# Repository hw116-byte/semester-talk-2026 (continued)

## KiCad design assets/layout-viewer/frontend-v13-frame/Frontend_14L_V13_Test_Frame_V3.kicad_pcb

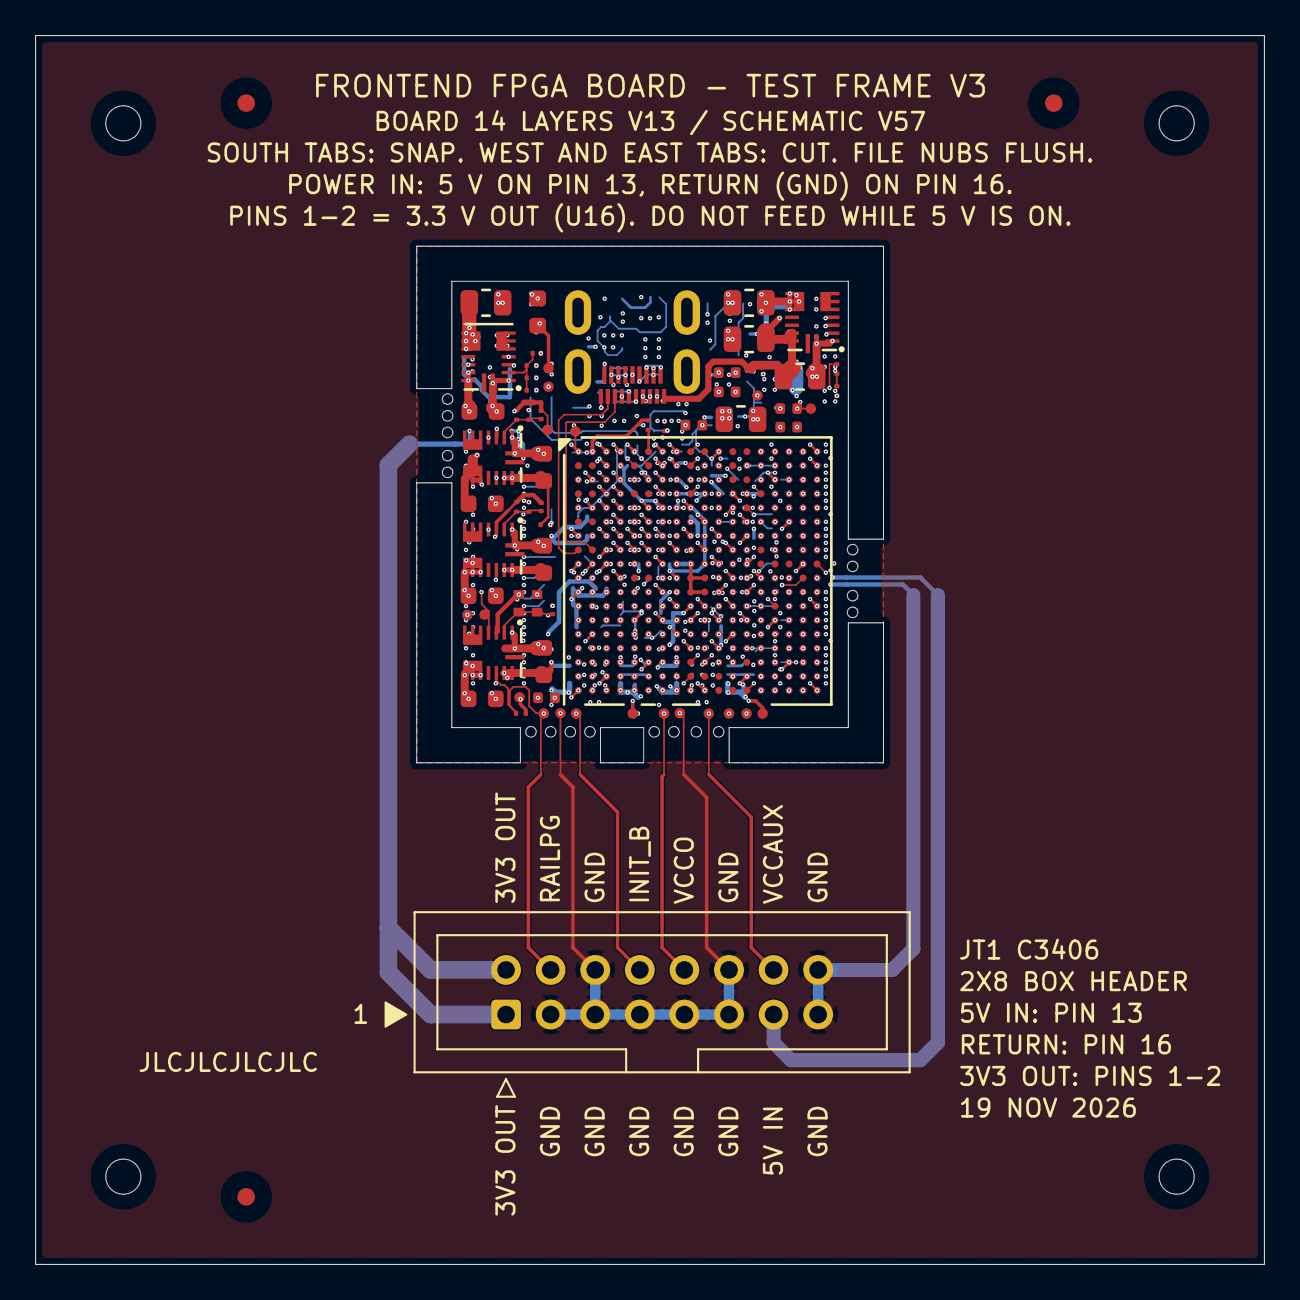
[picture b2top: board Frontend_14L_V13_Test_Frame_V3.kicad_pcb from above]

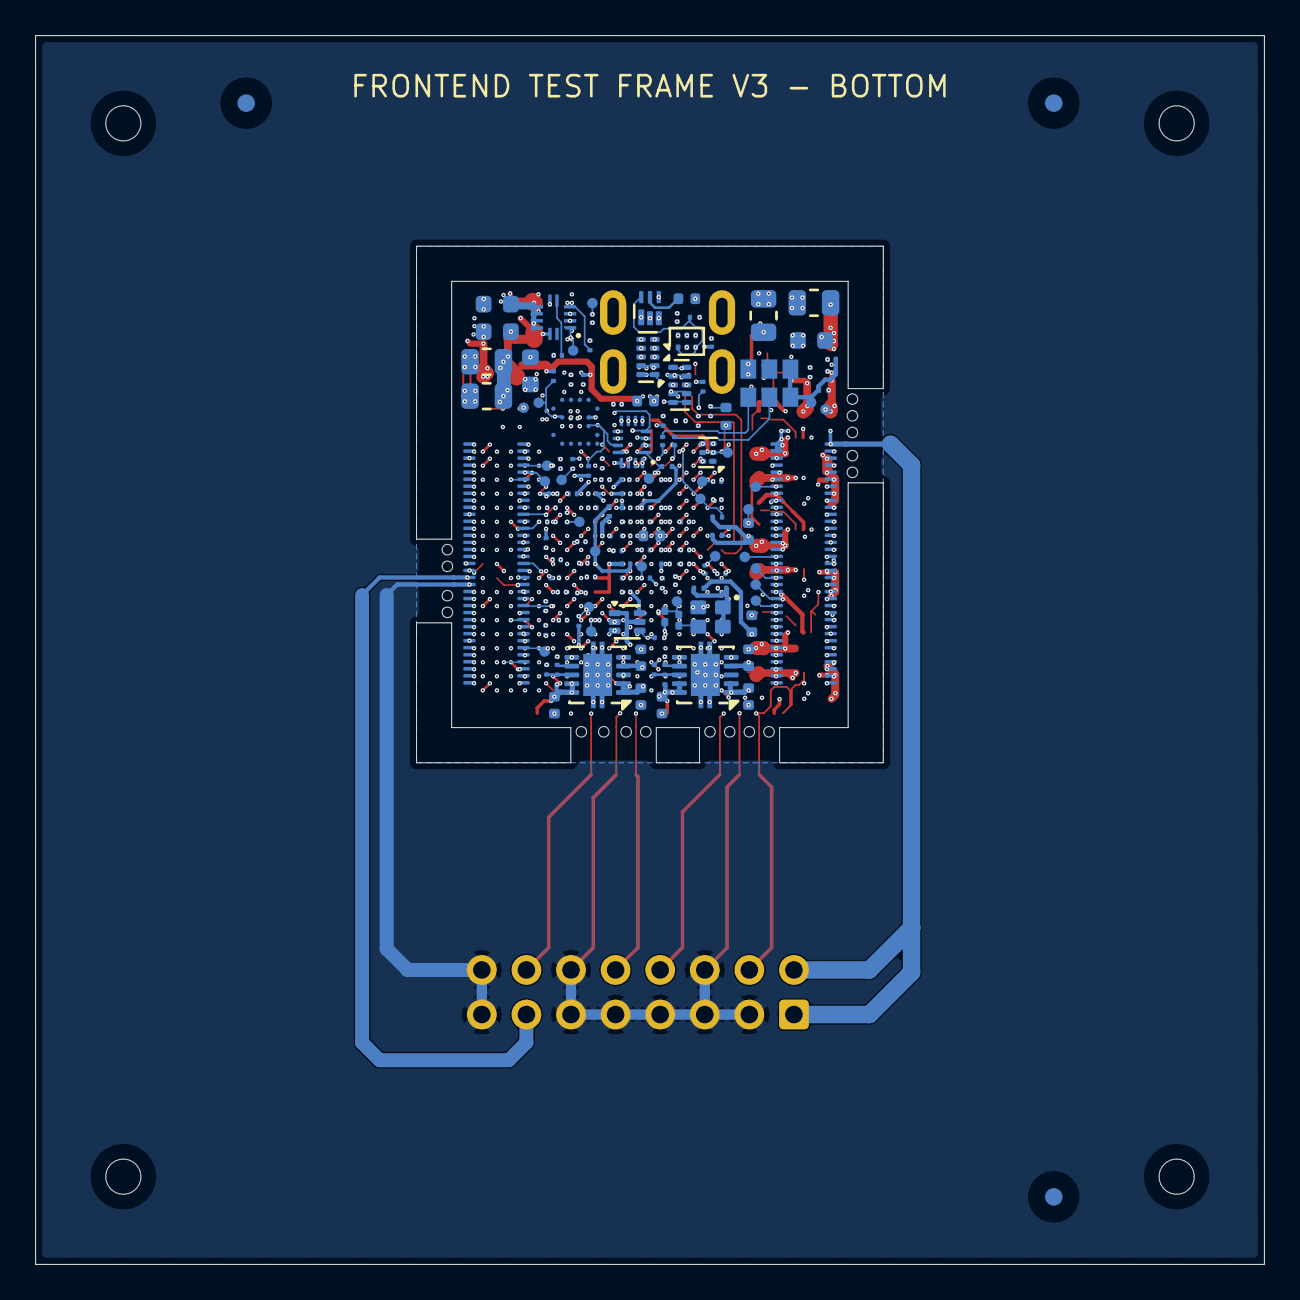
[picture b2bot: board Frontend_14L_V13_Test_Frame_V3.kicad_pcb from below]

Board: 14 copper layers, 70.0 x 70.0 mm, 233 parts (155 on the bottom side), 190 nets.

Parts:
C1, C2, C12, C13, C21, C22, C85, C86: 22uF; C_0603_1608Metric
C3, C14, C23, C87: 22pF; C_0201_GRM03_Murata_0p22Gap
C4, C89: 100uF; C_0805_2012Metric
C5, C6, C25, C36, C37, C51, C54, C96, C107: 4.7uF; C_0201_GRM03_Murata_0p22Gap
C7, C8, C9, C11, C18, C19, C20, C26, C27, C28, C29, C32, C33, C34, C35, C38, C39, C40, C52, C53, C55, C56, C57, C58, C80, C91, C92, C93, C97, C98, C99, C100: 470nF; C_0201_GRM03_Murata_0p22Gap
C10, C15, C42, C59: 47uF; C_0805_2012Metric
C16, C17, C24, C30, C31, C43, C44, C45, C47, C48, C49, C90, C94, C95, C101: 4.7uF; C_0402_1005Metric
C46, C50: 10nF; C_0201_GRM03_Murata_0p22Gap
C60, C63, C78, C79, C81, C82, C83, C88, C105, C106, C209: 100nF; C_0201_GRM03_Murata_0p22Gap
C61, C84: 1uF; C_0402_1005Metric
C62: 220nF; C_0201_GRM03_Murata_0p22Gap
C75, C76, C102, C104: 22uF / 6.3V; C_0603_1608Metric
C77: 22nF / 16V; C_0201_GRM03_Murata_0p22Gap
C103: 470nF / 6.3V; C_0201_GRM03_Murata_0p22Gap
C206, C207, C208: 22uF / 10V; C_0805_2012Metric
FID1, FID2, FID3, FID4, FID5, FID6: fiducial 1.0 mm, mask opening 2.0 mm
J1, J2: DF40C-70DS-0.4V(51); Hirose_DF40C-70DS-0.4V_2x35_P0.4mm
J3: Micro-HDMI 467651001; Molex_MicroHDMI_46765_1xxx
JT1: Box header 2x8 2.54mm (C3406); IDC-Header_2x08_P2.54mm_Vertical
L1, L2, L3, L4: MPZ0603S121HT000; TDK_MPZ0603S121HT000_0201_Land_0p25x0p30_Gap0p30
MB1, MB2, MB4: snap-off tab, 4 x 0.60 mm holes
MB3: snap-off tab, 5 x 0.60 mm holes
R1, R4, R5, R41, R55, R59: 200k; R_0201_ERA1A_Panasonic_0p30Gap
R2: 301k; R_0201_ERA1A_Panasonic_0p30Gap
R3, R9, R11, R14, R19, R22, R38, R43, R58: 4.99k; R_0201_ERA1A_Panasonic_0p30Gap
R7: 150k; R_0402_TE_CPF_Reflow_0p50Gap
R8: 100k; R_0402_TE_CPF_Reflow_0p50Gap
R10: 1.3k; R_0201_ERA1A_Panasonic_0p30Gap
R13: 2.49k; R_0201_ERA1A_Panasonic_0p30Gap
R16, R61, R62, R64: 100R; R_0201_ERA1A_Panasonic_0p30Gap
R17, R18, R20, R21, R49, R50: 4.7k; R_0201_ERA1A_Panasonic_0p30Gap
R25: 470R; R_0201_ERA1A_Panasonic_0p30Gap
R27: 1k; R_0201_ERA1A_Panasonic_0p30Gap
R37: 24k / 1%; R_0201_ERA1A_Panasonic_0p30Gap
R42: 150k; R_0201_ERA1A_Panasonic_0p30Gap
R44: 150R; R_0201_0603Metric
R45: 4.64k; R_0402_1005Metric
R46, R47, R48, R57: 10k; R_0201_ERA1A_Panasonic_0p30Gap
R51, R52, R53: 47k; R_0201_ERA1A_Panasonic_0p30Gap
R54: 22k; R_0201_ERA1A_Panasonic_0p30Gap
R60: 44.2k; R_0201_ERA1A_Panasonic_0p30Gap
R63: 680R; R_0201_0603Metric
TH1, TH2, TH3, TH4: tooling hole 2.0 mm, not plated
TP1, TP2, TP3, TP4, TP5, TP6, TP7, TP8, TP9, TP10, TP11, TP12, TP13, TP14, TP15, TP16, TP17, TP18, TP19, TP20, TP21, TP22, TP23, TP24, TP25, TP26, TP27, TP28, TP29, TP30, TP31, TP32, TP33, TP34, TP35, TP36, TP37, TP38, TP39, TP40, TP41, TP42, TP43, TP44, TP45, TP46, TP47: 0.6mm COPPER; TestPoint_Pad_D0.6mm_Edge_NoPaste
U1: XC7A35T-2CSG325C; Xilinx_CSG325
U2, U3, U4, U13, U16: MPM3833CGRH; MPS_QFN-18_2.5x3.5mm_MPM3833C
U5, U6: TPS74801DRCR; VSON-10-1EP_3x3mm_P0.5mm_EP1.65x2.4mm
U7: W25Q128JWYIQ; Winbond_WLCSP-21_P0.5mm
U8: SN74AVC4T774RSVR / SPI x1; TI_RSV_UQFN16_1.8x2.6mm_P0.4mm
U10: MP5077GG-Z; MPS_MP5077_QFN12_2x2mm_P0.4mm
U11: 74AUP2G07GM / dual reset OD; Nexperia_SOT886_XSON6_1x1.45mm
U12: TPS389001 / timed rail-ready reset; TI_DSE0006A_WSON6_1p5x1p5_P0p5_Manufacturer
U14: SN74AUP1G14 / SPI OE; Texas_USON-6_1x1.45mm_P0.5mm_SMD
U15: SN74AXC1T45DRLR; SOT-563
U17, U18: TPD4E02B04DQAR; USON-10_2.5x1.0mm_P0.5mm
Y1: AX3DAF1-125.0000T3 / 125 MHz; Abracon_AX3_3225_6pin
Y2: OT201625MJBA4SL / 25 MHz / 1.8 V; YXC_SMD2016-4P_2.0x1.6mm

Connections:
1V4_GTP_IN: C43.2, C47.2, C86.1, C87.1, R41.1, TP16.1 (PAD_1), U5.1 (IN), U5.2 (IN), U6.1 (IN), U6.2 (IN), U13.3, U13.8, U13.9, U13.10
/ASIC1_CLK32MHz_Out: J2.59, U1.R2 (L13P_T2_MRCC)
/ASIC1_DATA1: J2.21, U1.U2 (L15P_T2_DQS)
/ASIC1_DATA2: J2.64, U1.J4 (L2N_T0)
/ASIC1_DATA3: J2.62, U1.K2 (L3P_T0_DQS)
/ASIC1_DATA4: J2.60, U1.K1 (L3N_T0_DQS)
/ASIC1_DATA5: J2.57, U1.M1 (L7N_T1)
/ASIC1_DATA6: J2.55, U1.N1 (L9P_T1_DQS)
/ASIC1_DATA7: J2.53, U1.P1 (L9N_T1_DQS)
/ASIC1_DATA8: J2.51, U1.L3 (L5N_T0)
/ASIC1_READ: J2.49, U1.L2 (L4N_T0)
/ASIC1_SYNC: J2.61, U1.J5 (L2P_T0)
/ASIC2_CLK32MHz_Out: J1.63, TP29.1 (PAD_1), U1.D13 (L11P_T1_SRCC)
/ASIC2_DATA1: J1.70, U1.A17 (L15N_T2_DQS_ADV_B)
/ASIC2_DATA2: J1.51, U1.E15 (L13P_T2_MRCC)
/ASIC2_DATA3: J1.53, U1.D16 (L14N_T2_SRCC)
/ASIC2_DATA4: J1.55, U1.D15 (L13N_T2_MRCC)
/ASIC2_DATA5: J1.65, U1.B14 (L10P_T1_AD11P)
/ASIC2_DATA6: J1.67, U1.A15 (L10N_T1_AD11N)
/ASIC2_DATA7: J1.69, U1.A14 (L8N_T1_AD10N)
/ASIC2_DATA8: J1.38, U1.H17 (L23P_T3_FOE_B)
/ASIC2_READ: J1.40, U1.H18 (L23N_T3_FWE_B)
/ASIC2_SYNC: J1.61, TP33.1 (PAD_1), U1.B15 (L9N_T1_DQS_AD3N)
/ASIC3_4_TOP_SPI_CLK: J2.37, U1.P3 (L12N_T1_MRCC)
/ASIC3_4_TOP_SPI_LATCH: J2.35, U1.R7 (L22P_T3)
/ASIC3_CLK32MHz_Out: J2.25, U1.P4 (L12P_T1_MRCC)
/ASIC3_DATA1: J2.47, U1.L5 (L6P_T0)
/ASIC3_DATA2: J2.45, U1.M6 (L8P_T1)
/ASIC3_DATA3: J2.43, U1.N2 (L11N_T1_SRCC)
/ASIC3_DATA4: J2.39, U1.N6 (L8N_T1)
/ASIC3_DATA5: J2.23, U1.T2 (L14N_T2_SRCC)
/ASIC3_DATA6: J2.42, U1.D9 (L2P_T0_AD8P)
/ASIC3_DATA7: J1.39, U1.D14 (L12N_T1_MRCC)
/ASIC3_DATA8: J1.43, U1.G15 (L21P_T3_DQS)
/ASIC3_READ: J1.45, U1.F14 (L22N_T3_A16)
/ASIC3_SPI_DL: J2.33, U1.R5 (L21P_T3_DQS)
/ASIC3_SPI_DR: J2.31, U1.T7 (L22N_T3)
/ASIC3_SYNC: J2.29, U1.T3 (L17N_T2)
/ASIC4_CLK32MHz_Out: J1.56, U1.E16 (L14P_T2_SRCC)
/ASIC4_DATA1: J1.47, U1.F15 (L21N_T3_DQS_A18)
/ASIC4_DATA2: J1.49, U1.E13 (L12P_T1_MRCC)
/ASIC4_DATA3: J1.44, U1.G17 (L19P_T3_A22)
/ASIC4_DATA4: J1.46, U1.F17 (L24P_T3_RS1)
/ASIC4_DATA5: J1.58, U1.D18 (L17N_T2_A25)
/ASIC4_DATA6: J1.60, U1.C18 (L18N_T2_A23)
/ASIC4_DATA7: J1.62, U1.C17 (L18P_T2_A24)
/ASIC4_DATA8: J1.64, U1.B17 (L16N_T2_A27)
/ASIC4_READ: J1.68, U1.B16 (L15P_T2_DQS)
/ASIC4_SPI_DL: J1.48, U1.F18 (L19N_T3_A21_VREF)
/ASIC4_SPI_DR: J1.52, U1.E18 (L24N_T3_RS0)
/ASIC4_SYNC: J1.54, U1.E17 (L17P_T2_A26)
/ASIC5_CLK32MHz_Out: J2.12, U1.R3 (L14P_T2_SRCC)
/ASIC5_DATA1: J2.5, U1.V4 (L18N_T2)
/ASIC5_DATA2: J2.7, U1.U1 (L15N_T2_DQS)
/ASIC5_DATA3: J2.9, U1.U4 (L18P_T2)
/ASIC5_DATA4: J2.11, U1.U5 (L20N_T3)
/ASIC5_DATA5: J2.10, U1.T5 (L21N_T3_DQS)
/ASIC5_DATA6: J2.8, U1.T4 (L17P_T2)
/ASIC5_DATA7: J2.6, U1.U6 (L20P_T3)
/ASIC5_DATA8: J2.4, U1.U7 (L23P_T3)
/ASIC5_READ: J2.2, U1.V3 (L16P_T2)
/ASIC5_SYNC: J2.3, U1.V2 (L16N_T2)
/ASIC6_CLK32MHz_Out: J1.16, U1.R16 (L14P_T2_SRCC)
/ASIC6_DATA1: J1.1, U1.V16 (L18P_T2_A12_D28)
/ASIC6_DATA2: J1.28, U1.K18 (L3N_T0_DQS_EMCCLK)
/ASIC6_DATA3: J1.26, U1.L18 (L4N_T0_D05)
/ASIC6_DATA4: J1.24, U1.M17 (L7N_T1_D10)
/ASIC6_DATA5: J1.12, U1.R18 (L15P_T2_DQS_RDWR_B)
/ASIC6_DATA6: J1.10, U1.R17 (L14N_T2_SRCC)
/ASIC6_DATA7: J1.8, U1.T18 (L15N_T2_DQS_DOUT_CSO_B)
/ASIC6_DATA8: J1.6, U1.T17 (L16P_T2_CSI_B)
/ASIC6_READ: J1.4, U1.U17 (L16N_T2_A15_D31)
/ASIC6_SYNC: J1.18, U1.P18 (L10N_T1_D15)
/ASIC7_8_TOP_SPI_CLK: J2.24, TP43.1 (PAD_1), U1.N4 (L10N_T1)
/ASIC7_8_TOP_SPI_LATCH: J2.26, TP42.1 (PAD_1), U1.L4 (L5P_T0)
/ASIC7_CLK32MHz_Out: J2.36, U1.N3 (L11P_T1_SRCC)
/ASIC7_DATA1: J2.16, U1.R1 (L13N_T2_MRCC)
/ASIC7_DATA2: J2.18, U1.R6 (IO25)
/ASIC7_DATA3: J2.20, U1.P5 (L19N_T3_VREF)
/ASIC7_DATA4: J2.22, U1.P6 (L19P_T3)
/ASIC7_DATA5: J2.38, TP38.1 (PAD_1), U1.K3 (L4P_T0)
/ASIC7_DATA6: J2.40, U1.U9 (L24P_T3_A01_D17)
/ASIC7_DATA7: J1.37, U1.H16 (L20P_T3_A20)
/ASIC7_DATA8: J1.35, U1.V13 (L21N_T3_DQS_A06_D22)
/ASIC7_READ: J1.33, U1.T12 (L22P_T3_A05_D21)
/ASIC7_SPI_DL: J2.28, U1.M4 (L10P_T1)
/ASIC7_SPI_DR: J2.30, U1.M2 (L7P_T1)
/ASIC7_SYNC: J2.32, TP41.1 (PAD_1), U1.M5 (L6N_T0_VREF)
/ASIC8_CLK32MHz_Out: J1.13, U1.P15 (L11P_T1_SRCC)
/ASIC8_DATA1: J1.31, U1.U12 (L22N_T3_A04_D20)
/ASIC8_DATA2: J1.29, U1.K17 (L4P_T0_D04)
/ASIC8_DATA3: J1.25, U1.K15 (L5N_T0_D07)
/ASIC8_DATA4: J1.23, U1.L14 (IO0)
/ASIC8_DATA5: J1.11, TP47.1 (PAD_1), U1.R13 (L19P_T3_A10_D26)
/ASIC8_DATA6: J1.9, U1.T15 (L13N_T2_MRCC)
/ASIC8_DATA7: J1.7, U1.U14 (L20P_T3_A08_D24)
/ASIC8_DATA8: J1.5, U1.U16 (L17N_T2_A13_D29)
/ASIC8_READ: J1.3, U1.U15 (L17P_T2_A14_D30)
/ASIC8_SPI_DL: J1.21, U1.M16 (L7P_T1_D09)
/ASIC8_SPI_DR: J1.19, U1.N16 (L9P_T1_DQS)
/ASIC8_SYNC: J1.17, U1.P16 (L11N_T1_SRCC)
/BOARD3_SPI_LATCH: J1.36, U1.V14 (L20N_T3_A07_D23)
/CABLE_CLK_N: J3.8 (TX1_REC_N), R61.2, U1.R15 (L12N_T1_MRCC), U17.2, U17.9
/CABLE_CLK_P: J3.6 (TX1_REC_P), R61.1, U1.P14 (L12P_T1_MRCC), U17.1, U17.10
/CABLE_CMDSYNC_N: J3.11 (TX2_REC_N), R62.2, U1.N14 (L8N_T1_D12), U17.5, U17.6
/CABLE_CMDSYNC_P: J3.9 (TX2_REC_P), R62.1, U1.M14 (L8P_T1_D11), U17.4, U17.7
/CABLE_SYNC_N: J3.14 (GPIO_CMD_N), R64.2, U1.A9 (L3N_T0_DQS_AD1N), U18.2, U18.9
/CABLE_SYNC_P: J3.12 (GPIO_CMD_P), R64.1, U1.B9 (L3P_T0_DQS_AD1P), U18.1, U18.10
/CLK25_RAW: R44.1, Y2.3
/CLK25_VDD: C88.1, L3.2, Y2.1, Y2.4
/FB_GTP_1V4: C87.2, R41.2, R42.1, U13.2
/FB_VIN_3V3: R59.2, R60.1, U16.2
/FE_RESET_SHARED: J2.54, U1.D8 (L1P_T0_AD0P)
/IMP_TST_SHARED: J2.56, U1.C8 (L1N_T0_AD0N)
/STIM_CHIP1_SPI_DL: J2.46, U1.C11 (L4P_T0)
/STIM_CHIP1_SPI_DR: J2.44, U1.G14 (L22P_T3_A17)
/STIM_CHIP2_SPI_DL: J1.57, U1.C14 (L9P_T1_DQS_AD3P)
/STIM_CHIP3_SPI_DL: J2.17, U1.V7 (L24N_T3)
/STIM_CHIP4_SPI_DR: J1.20, U1.N18 (L10P_T1_D14)
BOARD1_CLK: J1.42, U1.G16 (L20N_T3_A19)
BOARD1_SPI_CLK: J2.52, U1.D10 (IO0)
BOARD1_SPI_LATCH: J2.48, U1.D11 (L6P_T0)
BOARD3_CLK: J1.2, U1.V17 (L18N_T2_A11_D27)
BOARD3_SPI_CLK: J2.13, U1.V8 (L24P_T3)
BOOT_RAILS_PG_3V3: JT1.4, R9.2, TP10.1 (PAD_1), U4.12, U5.3 (PG), U6.5 (EN), U12.3 (MR_PG)
BOOT_RESET_N: R47.2, TP28.1 (PAD_1), U11.1 (1A_RESET_N), U11.3 (2A_RESET_N), U12.6 (RESET_N_OD), U14.2
CABLE_TARGET_SENSE: J3.1 (SENSE), R27.2
CHIP_RESET_SHARED: J2.58, TP34.1 (PAD_1), U1.C9 (L2N_T0_AD8N)
CLK25_PL: R44.2, R63.1, TP44.1 (PAD_1), U1.T14 (L13P_T2_MRCC)
EN_GTPWR_1V5: R58.2, TP45.1 (PAD_1), U1.M15 (L6N_T0_D08_VREF), U15.3
EN_GTPWR_3V3: R57.1, U13.4, U15.4
FLASH_CS_N_1V8: R22.2, U7.1, U8.11 (B2_CS)
FLASH_DQ0_1V8: R53.2, TP25.1 (PAD_1), U7.5, U8.10 (B3_MOSI)
FLASH_DQ1_1V8: R51.1, U7.2, U8.9 (B4_MISO)
FLASH_HOLD_N_1V8: R21.2, U7.7
FLASH_READY_SENSE: R45.2, R46.1, U12.1 (SENSE_DIV)
FLASH_SCK_1V8: R52.1, U7.6, U8.12 (B1_SCK)
FLASH_TRANSLATOR_OE_N: R48.2, U8.7 (OE_N), U14.4
FLASH_WP_N_1V8: R20.2, U7.3
FPGA_DONE: R38.2, TP12.1 (PAD_1), U1.F12 (DONE_0)
FPGA_INIT_B: JT1.8, R18.2, TP11.1 (PAD_1), U1.T10 (INIT_B_0), U11.4 (2Y_INIT_OD)
FPGA_JTAG_TCK: J3.17 (TCK), U1.F8 (TCK_0)
FPGA_JTAG_TDI: J3.15 (TDI), U1.T9 (TDI_0)
FPGA_JTAG_TDO: J3.18 (TDO), U1.T8 (TDO_0)
FPGA_JTAG_TMS: J3.2 (TMS), U1.R8 (TMS_0)
FPGA_PROGRAM_B: R17.2, TP35.1 (PAD_1), U1.P10 (PROGRAM_B_0), U11.6 (1Y_PROGRAM_OD)
FPGA_PUDC_B: R25.2, U1.J18 (L3P_T0_DQS_PUDC_B)
FPGA_QSPI_CCLK: R49.2, TP30.1 (PAD_1), U1.E8 (CCLK_0), U8.1 (A1_CCLK)
FPGA_QSPI_CS_N: R19.2, U1.L15 (L6P_T0_FCS_B), U8.2 (A2_CS)
FPGA_QSPI_DQ0: R50.2, U1.K16 (L1P_T0_D00_MOSI), U8.3 (A3_MOSI)
FPGA_QSPI_DQ1: R54.1, U1.L17 (L1N_T0_D01_DIN), U8.4 (A4_MISO)
GND: C1.2, C2.2, C4.2, C5.2, C6.2, C7.2, C8.2, C9.2, C10.2, C11.2, C12.2, C13.2, C15.2, C16.2, C17.2, C18.2, C19.2, C20.2, C21.2, C22.2, C24.2, C25.2, C26.2, C27.2, C28.2, C29.2, C30.2, C31.2, C32.2, C33.2, C34.2, C35.2, C36.2, C37.2, C38.2, C39.2, C40.2, C42.2, C43.1, C44.2, C45.2, C46.2, C47.1, C48.2, C49.2, C50.2, C51.2, C52.2, C53.2, C54.2, C55.2, C56.2, C58.2, C59.2, C60.2, C61.2, C62.2, C63.2, C75.2, C76.2, C77.2, C80.2, C81.2, C82.2, C83.2, C84.2, C85.2, C86.2, C88.2, C89.2, C90.2, C91.2, C92.2, C93.2, C94.2, C95.2, C96.2, C97.2, C98.2, C99.2, C100.2, C101.2, C102.2, C103.2, C104.2, C105.2, C106.2, C107.2, C206.2, C207.2, C208.2, C209.2, J1.14, J1.15, J1.27, J1.30, J1.34, J1.41, J1.50, J1.66, J2.14, J2.15, J2.27, J2.34, J2.41, J2.50, J2.66, J3.4 (GND), J3.7 (GND), J3.10 (GND), J3.13 (GND), J3.16 (GND), J3.SH (SHIELD), JT1.3, JT1.5, JT1.6, JT1.7, JT1.9, JT1.11, JT1.12, JT1.15, JT1.16, L2.1, R2.2, R5.2, R8.2, R11.2, R14.2, R37.2, R42.2, R46.2, R51.2, R52.2, R54.2, R55.2, R57.2, R60.2, R63.2, TP1.1 (PAD_1), TP13.1 (PAD_1), TP15.1 (PAD_1), TP17.1 (PAD_1), TP18.1 (PAD_1), TP20.1 (PAD_1), TP21.1 (PAD_1), TP22.1 (PAD_1), TP26.1 (PAD_1), TP27.1 (PAD_1), TP31.1 (PAD_1), TP32.1 (PAD_1), TP36.1 (PAD_1), TP39.1 (PAD_1), TP40.1 (PAD_1), TP46.1 (PAD_1), U1.A1 (GND_[75_balls]), U1.A3 (MGTPRXN1_216), U1.A4 (MGTPRXP1_216), U1.A5 (GND), U1.A7 (GND), U1.A8 (GND), U1.A11 (GND), U1.A18 (GND), U1.B3 (GND), U1.B7 (GND), U1.B8 (GND), U1.B18 (GND), U1.C2 (GND), U1.C3 (MGTPRXN2_216), U1.C4 (MGTPRXP2_216), U1.C6 (GND), U1.C7 (GND), U1.C15 (GND), U1.D3 (GND), U1.D4 (GND), U1.D7 (GND), U1.D12 (GND), U1.E2 (GND), U1.E3 (MGTPRXN0_216), U1.E4 (MGTPRXP0_216), U1.E6 (GND), U1.E7 (GND), U1.E9 (GND), U1.E12 (CFGBVS_0), U1.F4 (GND), U1.F6 (GND), U1.F10 (GND), U1.F13 (M2_0), U1.F16 (GND), U1.G1 (GND), U1.G3 (MGTPRXN3_216), U1.G4 (MGTPRXP3_216), U1.G5 (GND), U1.G6 (GND), U1.G7 (GND), U1.G9 (GND), U1.G11 (GND), U1.G13 (GND), U1.H3 (GND), U1.H4 (GND), U1.H5 (GND), U1.H6 (GND), U1.H8 (GND), U1.H10 (GND), U1.H12 (GND), U1.J1 (GND), U1.J2 (GND), U1.J3 (GND), U1.J7 (GND), U1.J11 (GND), U1.J13 (GND), U1.J17 (GND), U1.K4 (GND), U1.K8 (GND), U1.K12 (GND), U1.K14 (GND), U1.L1 (GND), U1.L7 (GND), U1.L11 (GND), U1.L13 (GND), U1.M8 (GND), U1.M9 (DXN_0), U1.M10 (DXP_0), U1.M12 (GND), U1.M18 (GND), U1.N5 (GND), U1.N7 (GND), U1.N9 (GND), U1.N11 (GND), U1.N13 (GND), U1.N15 (GND), U1.P2 (GND), U1.P8 (GND), U1.P12 (GND), U1.R9 (GND), U1.R11 (M1_0), U1.T6 (GND), U1.T16 (GND), U1.U3 (GND), U1.U13 (GND), U1.V1 (GND), U1.V10 (GND), U1.V18 (GND), U2.1, U2.16, U3.1, U3.16, U4.1, U4.16, U5.6 (GND), U5.11 (GND_EP), U6.6 (GND), U6.11 (GND_EP), U7.4, U8.6 (DIR4_L), U8.8 (GND), U10.2 (GND), U11.2 (GND), U12.2 (GND), U13.1, U13.16, U14.3, U15.2, U16.1, U16.16, U17.3, U17.8, U18.3, U18.4, U18.5, U18.6, U18.7, U18.8, Y1.3 (GND), Y2.2
GNDADC_XADC: C57.2, L2.2, U1.J9 (GNDADC_0), U1.K9 (VREFN_0), U1.K10 (VP_0), U1.L9 (VN_0), U1.L10 (VREFP_0)
GTP_REFCLK1_N: C79.2, U1.B5 (MGTREFCLK1N_216)
GTP_REFCLK1_P: C78.2, U1.B6 (MGTREFCLK1P_216)
GTP_TX0_N: J3.3 (TX0_REC_P), U1.H1 (MGTPTXN0_216)
GTP_TX0_P: J3.5 (TX0_REC_N), U1.H2 (MGTPTXP0_216)
MGTAVCC_1V0: C45.1, C51.1, C52.1, C53.1, R10.1, TP7.1 (PAD_1), U1.B4 (MGTAVCC), U1.C5 (MGTAVCC), U1.E5 (MGTAVCC), U1.F5 (MGTAVCC), U5.9 (OUT), U5.10 (OUT)
MGTAVTT_1V2: C49.1, C54.1, C55.1, C56.1, R13.1, R16.1, TP8.1 (PAD_1), U1.A2 (MGTAVTT), U1.C1 (MGTAVTT), U1.E1 (MGTAVTT), U1.F3 (MGTAVTT), U1.G2 (MGTAVTT), U6.9 (OUT), U6.10 (OUT)
unnamed: R16.2, U1.A6 (MGTRREF_216)
unnamed: C3.2, R1.2, R2.1, U2.2
unnamed: C14.2, R4.2, R5.1, R55.1, U3.2
unnamed: C23.2, R7.2, R8.1, U4.2
unnamed: R10.2, R11.1, U5.8 (FB)
unnamed: C46.1, U5.7 (SS)
unnamed: R13.2, R14.1, U6.8 (FB)
unnamed: C50.1, U6.7 (SS)
unnamed: R37.1, U10.4 (ILIM)
unnamed: C77.1, U10.5 (SS)
unnamed: C84.1, U12.5 (CT)
OSC125_3V3: C80.1, C81.1, L4.2, TP24.1 (PAD_1), Y1.1 (OE), Y1.6 (VDD)
OSC125_N: C79.1, Y1.5 (OUTN)
OSC125_P: C78.1, Y1.4 (OUTP)
PG_AUX_1V8: TP19.1 (PAD_1), U3.12, U4.4
PG_CORE_1V0: R3.2, TP23.1 (PAD_1), U2.12, U3.4, U10.1 (EN)
PG_GTP_1V4: R43.2, U5.5 (EN), U13.12
STIM_CHB_SHARED: J2.1, U1.V9 (L24N_T3_A00_D16)
STIM_CHIP2_SPI_DR: J1.59, U1.C16 (L16P_T2_A28)
STIM_CHIP3_SPI_DR: J2.19, U1.V6 (L23N_T3)
STIM_CHIP4_SPI_DL: J1.22, U1.N17 (L9N_T1_DQS_D13)
STIM_CLK_SHARED: J2.65, U1.B11 (L4N_T0)
STIM_EN_SHARED: J2.63, U1.J6 (IO0)
STIM_START_SHARED: J2.67, U1.B10 (L5P_T0_AD9P)
SWITCHED_3V3: C76.1, C104.1, C106.1, L4.1, TP3.1 (PAD_1), U10.7 (VOUT), U10.8 (VOUT), U10.9 (VOUT), U10.10 (VOUT), U15.6
VCCADC_1V8: C57.1, L1.2, TP37.1 (PAD_1), U1.J10 (VCCADC_0)
VCCAUX_1V8: C13.1, C14.1, C15.1, C16.1, C17.1, C18.1, C19.1, C20.1, C58.1, C59.1, C60.1, C62.1, C94.1, C95.1, C96.1, C97.1, C98.1, C99.1, C100.1, JT1.14, L1.1, L3.1, R4.1, R17.1, R18.1, R20.1, R21.1, R22.1, R27.1, R38.1, R45.1, R49.1, R53.1, TP5.1 (PAD_1), TP9.1 (PAD_1), U1.E10 (VCCO_0), U1.E11 (VCCBATT_0), U1.G12 (VCCAUX_[5_balls]), U1.H13 (VCCAUX), U1.K13 (VCCAUX), U1.M13 (VCCAUX), U1.P13 (VCCAUX), U1.R10 (VCCO_0), U1.R12 (M0_0), U3.3, U3.8, U3.9, U3.10, U7.8, U8.13 (VCCB_1V8)
VCCINT_1V0: C2.1, C3.1, C4.1, C5.1, C6.1, C7.1, C8.1, C9.1, C10.1, C11.1, C89.1, C90.1, C91.1, C92.1, C93.1, R1.1, TP4.1 (PAD_1), U1.F7 (VCCINT_1V0), U1.F9 (VCCINT_1V0), U1.F11 (VCCBRAM/VCCINT_[21_balls]), U1.G8 (VCCINT_1V0), U1.G10 (VCCBRAM_1V0), U1.H7 (VCCINT_1V0), U1.H9 (VCCINT_1V0), U1.H11 (VCCBRAM_1V0), U1.J8 (VCCINT_1V0), U1.J12 (VCCINT_1V0), U1.K7 (VCCINT_1V0), U1.K11 (VCCINT_1V0), U1.L8 (VCCINT_1V0), U1.L12 (VCCINT_1V0), U1.M7 (VCCINT_1V0), U1.M11 (VCCINT_1V0), U1.N8 (VCCINT_1V0), U1.N10 (VCCINT_1V0), U1.N12 (VCCINT_1V0), U1.P9 (VCCINT_1V0), U1.P11 (VCCINT_1V0), U2.3, U2.8, U2.9, U2.10
VCCO_1V5: C22.1, C23.1, C24.1, C25.1, C26.1, C27.1, C28.1, C29.1, C30.1, C31.1, C32.1, C33.1, C34.1, C35.1, C36.1, C37.1, C38.1, C39.1, C40.1, C42.1, C61.1, C63.1, C101.1, C105.1, C107.1, JT1.10, R7.1, R19.1, R25.1, R48.1, R50.1, R58.1, TP6.1 (PAD_1), U1.A16 (VCCO), U1.B13 (VCCO), U1.C10 (VCCO), U1.D17 (VCCO), U1.E14 (VCCO), U1.G18 (VCCO), U1.H15 (VCCO), U1.L6 (VCCO), U1.L16 (VCCO), U1.M3 (VCCO), U1.P7 (VCCO), U1.P17 (VCCO), U1.R4 (VCCO), U1.R14 (VCCO), U1.T1 (VCCO), U1.T11 (VCCO), U1.U8 (VCCO), U1.U18 (VCCO), U1.V5 (VCCO), U1.V15 (VCCO), U4.3, U4.8, U4.9, U4.10, U8.5 (DIR3_H), U8.14 (VCCA_1V5), U8.15 (DIR1_H), U8.16 (DIR2_H), U14.6, U15.1, U15.5
VIN_3V3: C1.1, C12.1, C21.1, C44.1, C48.1, C75.1, C82.1, C83.1, C85.1, C102.1, C103.1, C208.1, J2.68, J2.69, J2.70, JT1.1, JT1.2, R3.1, R9.1, R43.1, R47.1, R59.1, TP2.1 (PAD_1), U2.4, U2.13, U2.14, U3.13, U3.14, U4.13, U4.14, U5.4 (BIAS), U6.4 (BIAS), U10.3 (VCC), U10.6 (VIN), U10.11 (VIN), U11.5 (VCC_3V3), U12.4 (VDD_3V3), U13.13, U13.14, U16.3, U16.8, U16.9, U16.10
VIN_5V: C206.1, C207.1, C209.1, J1.32, J3.19 (5V_IN), JT1.13, TP14.1 (PAD_1), U16.4, U16.13, U16.14

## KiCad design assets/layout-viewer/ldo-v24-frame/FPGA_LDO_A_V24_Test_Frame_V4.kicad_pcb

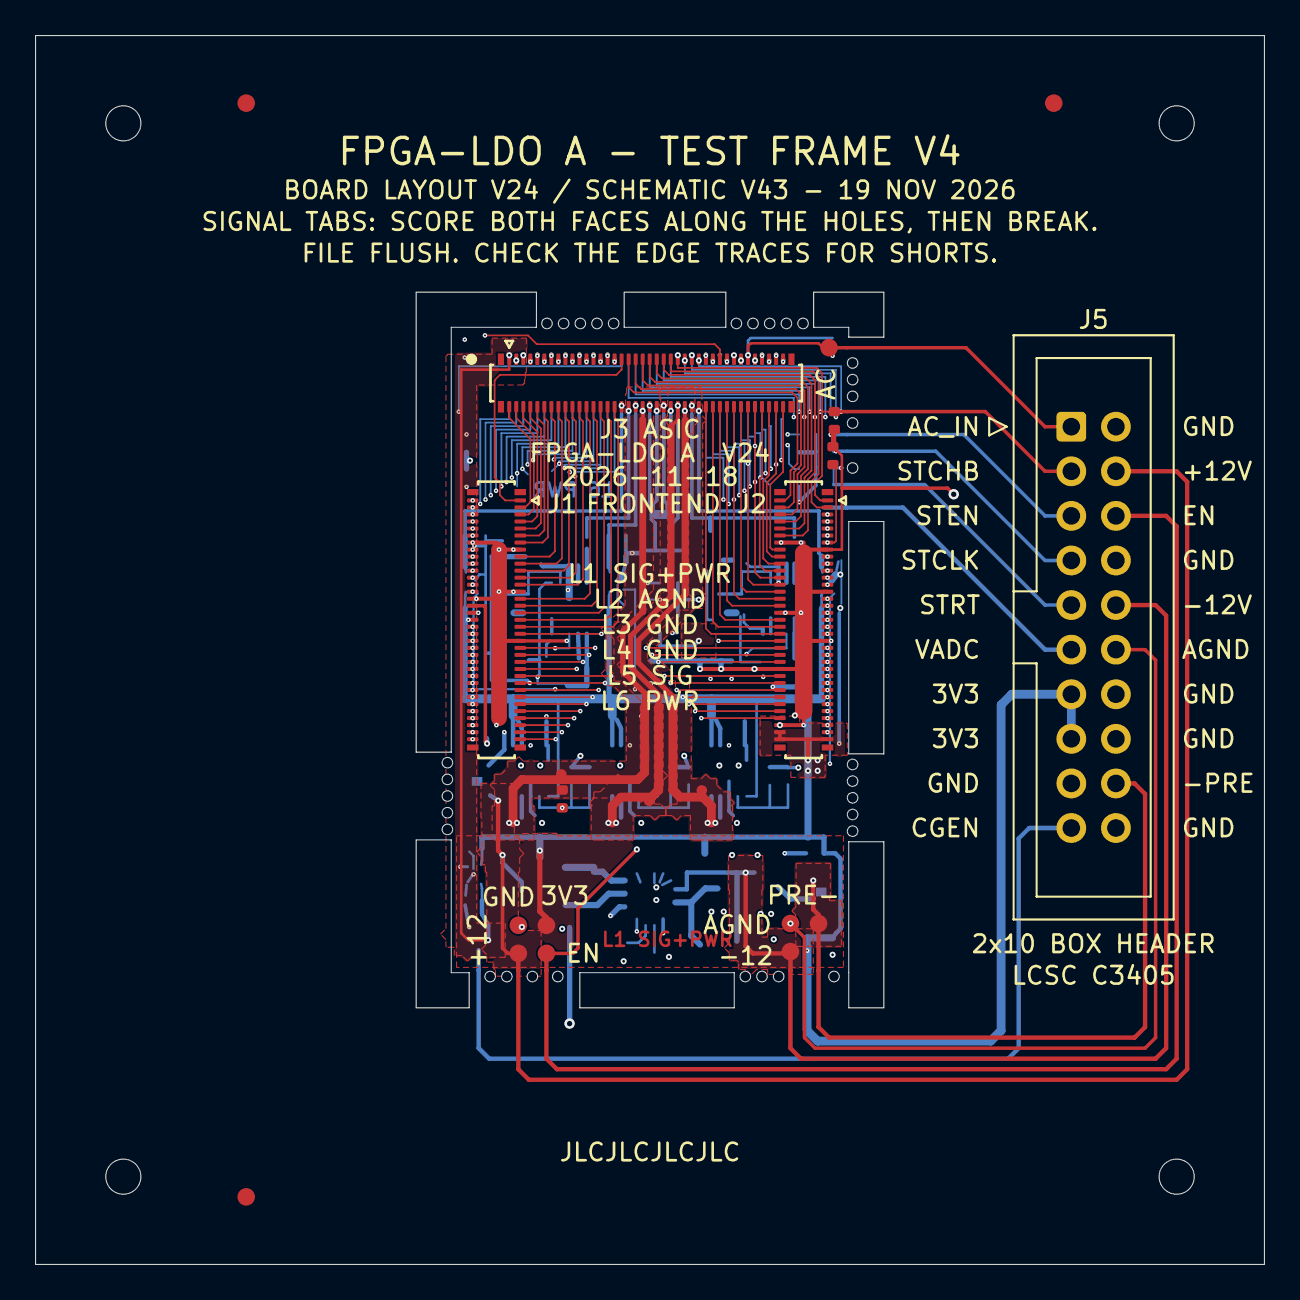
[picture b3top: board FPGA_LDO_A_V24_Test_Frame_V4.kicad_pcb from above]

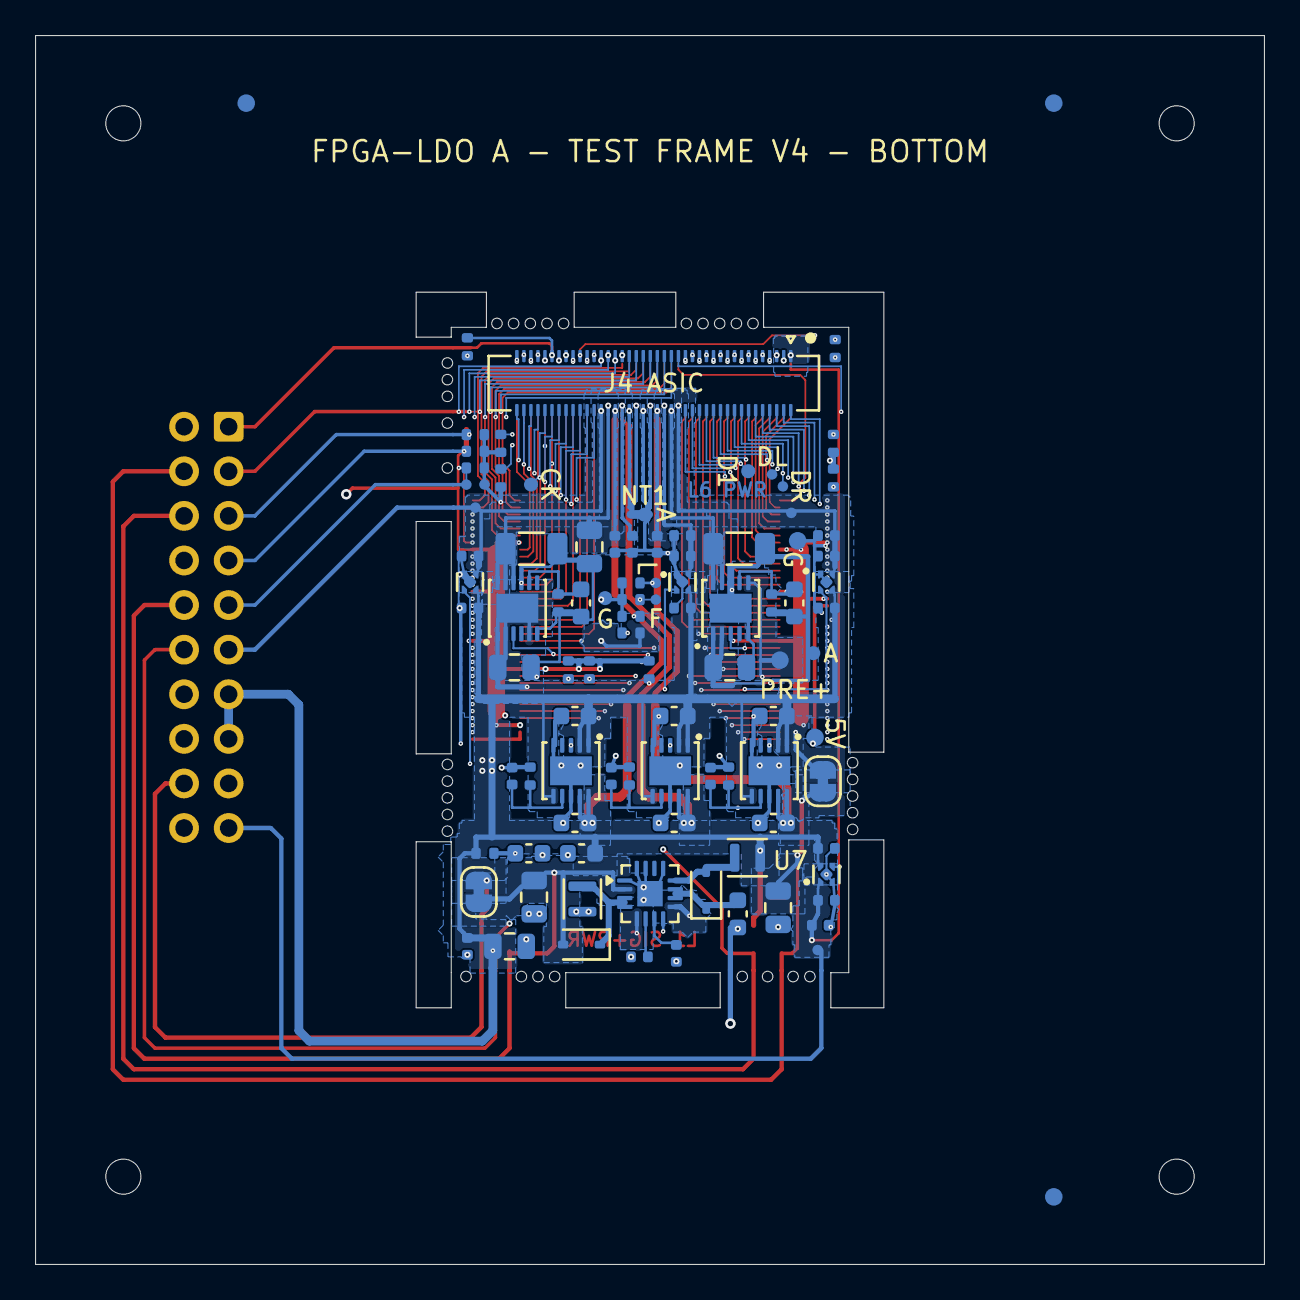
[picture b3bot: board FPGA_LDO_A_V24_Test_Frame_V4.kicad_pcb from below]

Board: 6 copper layers, 70.0 x 70.0 mm, 131 parts (99 on the bottom side), 150 nets.

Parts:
C1, C14, C21: 22uF; C_0805_2012Metric
C2: 100nF; C_0402_1005Metric
C3, C11: 4.7uF; C_0603_1608Metric
C15, C903, C1003: 1uF; C_0603_1608Metric
C16, C17: 10nF; C_0402_1005Metric
C51, C53, C54, C55, C56, C57, C203, C301, C302, C401, C402, C501, C502, C603, C701, C702, C803: 1uF; C_0402_1005Metric
C201, C202, C601, C602, C801, C802: 10uF; C_0603_1608Metric
C901, C1001, C1004: 10uF; C_0805_2012Metric
C902, C1002: 22uF; C_1206_3216Metric
D11, D12: B0540WS-TP; D_SOD-323
FID1, FID2, FID3, FID4, FID5, FID6: fiducial 1.0 mm, mask opening 2.0 mm
J1, J2: DF40C-70DP-0.4V(51); Hirose_DF40C-70DP-0.4V_2x35-1MP_P0.4mm
J3: DF40C-80DP-0.4V(51); Hirose_DF40C-80DP-0.4V_2x40-1MP_P0.4mm
J4: DF40C-80DS-0.4V(51); Hirose_DF40C-80DS-0.4V_2x40_P0.4mm
J5: 2x10 2.54 mm box header; IDC-Header_2x10_P2.54mm_Vertical
JP1, JP2: Bridged; SolderJumper-2_P1.3mm_Bridged_RoundedPad1.0x1.5mm
L11, L12: 6.8uH; L_Murata_DFE201610P
MB1: mech tab N1, 5 x 0.60 mm holes
MB2: mech tab N2, 5 x 0.60 mm holes
MB3: mech tab W1, 5 x 0.60 mm holes
MB4: mech tab E2, 5 x 0.60 mm holes
MB5: signal tab SW, 4 x 0.60 mm holes
MB6: signal tab SE, 4 x 0.60 mm holes
MB7: signal tab E, 5 x 0.60 mm holes
NT1: NetTie_2; NetTie-2_SMD_Pad0.5mm
R1, R2, R3, R4, R5, R6, R16, R17, R18, R19, R20, R21, R22, R23, R24, R25, R26, R27, R28: 10k; R_0402_1005Metric
R201, R601: 15k; R_0402_1005Metric
R801: 7.5k; R_0402_1005Metric
R802: 47k; R_0402_1005Metric
R901, R1001: 80.6k; R_0402_1005Metric
TH1, TH2, TH3, TH4: tooling hole 2.0 mm, not plated
TP1: VIN_3V3; TestPoint_Pad_D1.0mm_Compact
TP2: STIM_POS_12V; TestPoint_Pad_D1.0mm_Compact
TP3: STIM_NEG_12V; TestPoint_Pad_D1.0mm_Compact
TP4: EN_ASIC_RAILS; TestPoint_Pad_D1.0mm_Compact
TP5: GND; TestPoint_Pad_D1.0mm_Compact
TP6: AGND; TestPoint_Pad_D1.0mm_Compact
TP7: ASIC_AC_IN; TestPoint_Pad_D1.0mm_Compact
TP8: STIM_PRE_POS; TestPoint_Pad_D1.0mm_Compact
TP9: STIM_PRE_NEG; TestPoint_Pad_D1.0mm_Compact
TP10: VIN_5V; TestPoint_Pad_D1.0mm_Compact
TP11: ASIC_VDD_FE; TestPoint_Pad_D0.6mm_Compact
TP12: ASIC_VDD_ADC; TestPoint_Pad_D0.6mm_Compact
TP14: ASIC_DVDD; TestPoint_Pad_D0.6mm_Compact
TP15: ASIC_REF_VDD; TestPoint_Pad_D0.6mm_Compact
TP16: ASIC_VDD_CGEN; TestPoint_Pad_D0.6mm_Compact
TP17: ASIC_REF_VCM; TestPoint_Pad_D0.6mm_Compact
TP20: ASIC4_SPI_DR; TestPoint_Pad_D0.6mm_Compact
TP21: ASIC4_SPI_DL; TestPoint_Pad_D0.6mm_Compact
TP22: ASIC4_DATA1; TestPoint_Pad_D0.8mm_Compact015
TP23: GND; TestPoint_Pad_D1.0mm_Compact015
TP24: ASIC3_4_TOP_SPI_CLK; TestPoint_Pad_D0.8mm_Compact015
TP25: STIM_START_SHARED; TestPoint_Pad_D0.6mm_Compact
TP26: GND; TestPoint_Pad_D0.6mm_Compact
TP27: BOARD1_SPI_LATCH; TestPoint_Pad_D0.6mm_Compact
TP28: FE_RESET_SHARED; TestPoint_Pad_D0.6mm_Compact
TP29: GND; TestPoint_Pad_D0.8mm_Compact015
TP30, TP31: AGND; TestPoint_Pad_D0.8mm_Compact015
U1: LT3582EUD-12#PBF; QFN-16-1EP_3x3mm_P0.5mm_EP1.45x1.45mm
U2, U6, U8, U9: LT3042EDD#PBF; DFN-10-1EP_3x3mm_P0.5mm_EP1.65x2.38mm
U3, U4, U5, U7: TPS7A2015PDQNR; Texas_X2SON-4_1x1mm_P0.65mm
U10: LT3094EDD#PBF; DFN-12-1EP_3x3mm_P0.45mm_EP1.65x2.38mm

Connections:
/ASIC1_CLK32MHz_Out: J2.59, J4.45
/ASIC1_DATA1: J2.21, J4.79
/ASIC1_DATA2: J2.64, J4.77
/ASIC1_DATA3: J2.62, J4.75
/ASIC1_DATA4: J2.60, J4.73
/ASIC1_DATA5: J2.57, J4.43
/ASIC1_DATA6: J2.55, J4.41
/ASIC1_DATA7: J2.53, J4.39
/ASIC1_DATA8: J2.51, J4.37
/ASIC1_READ: J2.49, J4.35
/ASIC1_SYNC: J2.61, J4.47
/ASIC2_CLK32MHz_Out: J1.63, J4.19
/ASIC2_DATA1: J1.70, J4.33
/ASIC2_DATA2: J1.51, J4.31
/ASIC2_DATA3: J1.53, J4.29
/ASIC2_DATA4: J1.55, J4.27
/ASIC2_DATA5: J1.65, J4.17
/ASIC2_DATA6: J1.67, J4.15
/ASIC2_DATA7: J1.69, J4.13
/ASIC2_DATA8: J1.38, J4.11
/ASIC2_READ: J1.40, J4.9
/ASIC2_SYNC: J1.61, J4.21
/ASIC3_4_TOP_SPI_CLK: J2.37, J4.72, R24.1, TP24.1
/ASIC3_4_TOP_SPI_LATCH: J2.35, J4.70, R26.1
/ASIC3_CLK32MHz_Out: J2.25, J4.62
/ASIC3_DATA1: J2.47, J4.80
/ASIC3_DATA2: J2.45, J4.78
/ASIC3_DATA3: J2.43, J4.76
/ASIC3_DATA4: J2.39, J4.74
/ASIC3_DATA5: J2.23, J4.60
/ASIC3_DATA6: J2.42, J4.58
/ASIC3_DATA7: J1.39, J4.32
/ASIC3_DATA8: J1.43, J4.30
/ASIC3_READ: J1.45, J4.28
/ASIC3_SPI_DL: J2.33, J4.68
/ASIC3_SPI_DR: J2.31, J4.66
/ASIC3_SYNC: J2.29, J4.64
/ASIC4_CLK32MHz_Out: J1.56, J4.12
/ASIC4_DATA1: J1.47, J4.26, TP22.1
/ASIC4_DATA2: J1.49, J4.24
/ASIC4_DATA3: J1.44, J4.22
/ASIC4_DATA4: J1.46, J4.20
/ASIC4_DATA5: J1.58, J4.10
/ASIC4_DATA6: J1.60, J4.8
/ASIC4_DATA7: J1.62, J4.6
/ASIC4_DATA8: J1.64, J4.4
/ASIC4_READ: J1.68, J4.2
/ASIC4_SPI_DL: J1.48, J4.18, TP21.1
/ASIC4_SPI_DR: J1.52, J4.16, TP20.1
/ASIC4_SYNC: J1.54, J4.14
/ASIC5_CLK32MHz_Out: J2.12, J3.45
/ASIC5_DATA1: J2.5, J3.79
/ASIC5_DATA2: J2.7, J3.77
/ASIC5_DATA3: J2.9, J3.75
/ASIC5_DATA4: J2.11, J3.73
/ASIC5_DATA5: J2.10, J3.43
/ASIC5_DATA6: J2.8, J3.41
/ASIC5_DATA7: J2.6, J3.39
/ASIC5_DATA8: J2.4, J3.37
/ASIC5_READ: J2.2, J3.35
/ASIC5_SYNC: J2.3, J3.47
/ASIC6_CLK32MHz_Out: J1.16, J3.19
/ASIC6_DATA1: J1.1, J3.33
/ASIC6_DATA2: J1.28, J3.31
/ASIC6_DATA3: J1.26, J3.29
/ASIC6_DATA4: J1.24, J3.27
/ASIC6_DATA5: J1.12, J3.17
/ASIC6_DATA6: J1.10, J3.15
/ASIC6_DATA7: J1.8, J3.13
/ASIC6_DATA8: J1.6, J3.11
/ASIC6_READ: J1.4, J3.9
/ASIC6_SYNC: J1.18, J3.21
/ASIC7_8_TOP_SPI_CLK: J2.24, J3.72, R25.1
/ASIC7_8_TOP_SPI_LATCH: J2.26, J3.70, R27.1
/ASIC7_CLK32MHz_Out: J2.36, J3.62
/ASIC7_DATA1: J2.16, J3.80
/ASIC7_DATA2: J2.18, J3.78
/ASIC7_DATA3: J2.20, J3.76
/ASIC7_DATA4: J2.22, J3.74
/ASIC7_DATA5: J2.38, J3.60
/ASIC7_DATA6: J2.40, J3.58
/ASIC7_DATA7: J1.37, J3.32
/ASIC7_DATA8: J1.35, J3.30
/ASIC7_READ: J1.33, J3.28
/ASIC7_SPI_DL: J2.28, J3.68
/ASIC7_SPI_DR: J2.30, J3.66
/ASIC7_SYNC: J2.32, J3.64
/ASIC8_CLK32MHz_Out: J1.13, J3.12
/ASIC8_DATA1: J1.31, J3.26
/ASIC8_DATA2: J1.29, J3.24
/ASIC8_DATA3: J1.25, J3.22
/ASIC8_DATA4: J1.23, J3.20
/ASIC8_DATA5: J1.11, J3.10
/ASIC8_DATA6: J1.9, J3.8
/ASIC8_DATA7: J1.7, J3.6
/ASIC8_DATA8: J1.5, J3.4
/ASIC8_READ: J1.3, J3.2
/ASIC8_SPI_DL: J1.21, J3.18
/ASIC8_SPI_DR: J1.19, J3.16
/ASIC8_SYNC: J1.17, J3.14
/ASIC_AC_IN: J3.69, J4.69, J5.1, R6.1, TP7.1
/ASIC_DVDD: C54.1, C502.1, J3.34, J4.34, R19.2, TP14.1, U5.1
/ASIC_REF_VCM: C57.1, C802.1, J3.40, J4.40, R802.1, TP17.1, U8.9, U8.10
/ASIC_REF_VDD: C55.1, C602.1, J3.52, J4.52, TP15.1, U6.9, U6.10
/ASIC_VDD10: C902.1, J3.36, J4.36, U9.9, U9.10
/ASIC_VDD_ADC: C302.1, J3.56, J4.56, J5.11, TP12.1, U3.1
/ASIC_VDD_CGEN: C56.1, C702.1, J3.1, J4.1, J5.19, TP16.1, U7.1
/ASIC_VDD_DRIVER: C53.1, C402.1, J3.38, J4.38, U4.1
/ASIC_VDD_FE: C51.1, C202.1, J3.50, J4.50, TP11.1, U2.9, U2.10
/ASIC_VSS10: C1002.1, C1004.1, J3.54, J4.54, U10.10, U10.11, U10.12
/BOARD1_CLK: J1.42, J4.7, R20.1
/BOARD1_SPI_CLK: J2.52, J4.63, R22.1
/BOARD1_SPI_LATCH: J2.48, J4.61, R18.1, TP27.1
/BOARD3_CLK: J1.2, J3.7, R21.1
/BOARD3_SPI_CLK: J2.13, J3.63, R23.1
/BOARD3_SPI_LATCH: J1.36, J3.61, R28.1
/CAPP: C15.1, D11.1, U1.10, U1.11
/CHIP_RESET_SHARED: J2.58, J3.71, J4.71, R19.1
/EN_ASIC_RAILS: C3.1, J5.6, R1.2, TP4.1, U1.8, U2.3, U3.3, U4.3, U5.3, U6.3, U7.3, U8.3, U9.3, U10.3
/FE_RESET_SHARED: J2.54, J3.65, J4.65, R16.1, TP28.1
/IMP_TST_SHARED: J2.56, J3.67, J4.67, R17.1
/RAMPN: C17.1, U1.6
/RAMPP: C16.1, U1.7
/STIM_CHB_SHARED: J2.1, J3.49, J4.49, J5.3, R4.1
/STIM_CHIP1_SPI_DL: J2.46, J4.59
/STIM_CHIP1_SPI_DR: J2.44, J4.57
/STIM_CHIP2_SPI_DL: J1.57, J4.25
/STIM_CHIP2_SPI_DR: J1.59, J4.23
/STIM_CHIP3_SPI_DL: J2.17, J3.59
/STIM_CHIP3_SPI_DR: J2.19, J3.57
/STIM_CHIP4_SPI_DL: J1.22, J3.25
/STIM_CHIP4_SPI_DR: J1.20, J3.23
/STIM_CLK_SHARED: J2.65, J3.53, J4.53, J5.7, R5.1
/STIM_EN_SHARED: J2.63, J3.51, J4.51, J5.5, R2.1
/STIM_NEG_12V: C21.1, D12.2, J5.10, JP2.1, TP3.1, U1.2
/STIM_POS_12V: C14.1, J5.4, JP1.1, TP2.1, U1.9
/STIM_PRE_NEG: C1001.1, J5.18, JP2.2, TP9.1, U10.1, U10.2, U10.5, U10.13
/STIM_PRE_POS: C901.1, JP1.2, TP8.1, U9.1, U9.2, U9.6
/STIM_START_SHARED: J2.67, J3.55, J4.55, J5.9, R3.1, TP25.1
/SW_N: D12.1, L12.1, U1.3, U1.4
/SW_P: D11.2, L11.2, U1.12
/VIN_3V3: C1.1, C2.1, C11.1, C201.1, C301.1, C401.1, C501.1, C601.1, C701.1, C801.1, J2.68, J2.69, J2.70, J5.13, J5.15, L11.1, R1.1, TP1.1, U1.5, U2.1, U2.2, U2.6, U3.4, U4.4, U5.4, U6.1, U6.2, U6.6, U7.4, U8.1, U8.2, U8.6
/VIN_5V: J1.32, TP10.1
AGND: C51.2, C53.2, C55.2, C56.2, C57.2, C201.2, C202.2, C203.2, C301.2, C302.2, C401.2, C402.2, C601.2, C602.2, C603.2, C701.2, C702.2, C801.2, C802.2, C803.2, C901.2, C902.2, C903.2, C1001.2, C1002.2, C1003.2, C1004.2, J3.42, J3.44, J4.42, J4.44, J5.12, NT1.2, R6.2, R201.2, R601.2, R801.2, R802.2, R901.2, R1001.2, TP6.1, TP30.1, TP31.1, U2.5, U2.8, U2.11, U3.2, U3.5, U4.2, U4.5, U6.5, U6.8, U6.11, U7.2, U7.5, U8.5, U8.8, U8.11, U9.5, U9.8, U9.11, U10.6, U10.9
GND: C1.2, C2.2, C3.2, C11.2, C14.2, C15.2, C16.2, C17.2, C21.2, C54.2, C501.2, C502.2, J1.14, J1.15, J1.27, J1.30, J1.34, J1.41, J1.50, J1.66, J2.14, J2.15, J2.27, J2.34, J2.41, J2.50, J2.66, J3.3, J3.5, J3.46, J3.48, J4.3, J4.5, J4.46, J4.48, J5.2, J5.8, J5.14, J5.16, J5.17, J5.20, L12.2, NT1.1, R2.2, R3.2, R4.2, R5.2, R16.2, R17.2, R18.2, R20.2, R21.2, R22.2, R23.2, R24.2, R25.2, R26.2, R27.2, R28.2, TP5.1, TP23.1, TP26.1, TP29.1, U1.1, U1.13, U1.15, U1.16, U1.17, U5.2, U5.5
unnamed: C203.1, R201.1, U2.7
unnamed: C603.1, R601.1, U6.7
unnamed: C803.1, R801.1, U8.7
unnamed: C903.1, R901.1, U9.7
unnamed: C1003.1, R1001.1, U10.8
